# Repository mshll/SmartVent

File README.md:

# LaunchPilot: Smart Vent

Senior Capstone Project (Spring 2024)

Industry Sponsor: Cedrec Sumimoto

Faculty Advisor: Andrew Greenberg

Team members: Meshal Almutairi, Michael Fontaine, Abdulaziz Alateeqi,
Fawzan Alfahad, John Michael Mertz

## Overview

We teamed up with Launch Pilot to make a smart vent system. The main goal was to ensure safe indoor air quality by monitoring CO2 levels. When the CO2 level goes above the safe threshold, the system automatically activates to circulate fresh clean air into the room, thus reducing the CO2 level.

## Approach

We designed the system using sensors to detect CO2 levels, temperature, and
humidity. The design also includes fans that operate at different speeds to help with fresh air circulations, an LCD to display the sensor readings, and a microcontroller as the brain of this project. We also implemented a web-based dashboard that is accessible via a local network for remote monitoring and adjustments such as changing the CO2 level threshold, turning the system entirely on or off, and controlling the fan's speed. Additionally, we integrated buttons on the fans to provide direct control for the different settings.

## Results

Our system successfully reads carbon dioxide levels and activates the fans accordingly. Moreover, the web-based dashboard and the buttons work great when adjusting different settings. The LCD provides real-time readings from the sensors as well as any warnings. Users can control the system directly or remotely, which has been a major plus.

## Completed Build

## Dashboard Preview

## Device OLED Display Preview

## Project Report

For more details on the project, please refer to the [Project Report](Documents/Smart_Vent_Report.pdf)

## User Manual

For instructions on how to use the system, please refer to the [User Manual](Documents/Smart_Vent_User_Manual.pdf)

## License

This project is licensed under the AGPL-3.0 License - see the [LICENSE](LICENSE) file for details.

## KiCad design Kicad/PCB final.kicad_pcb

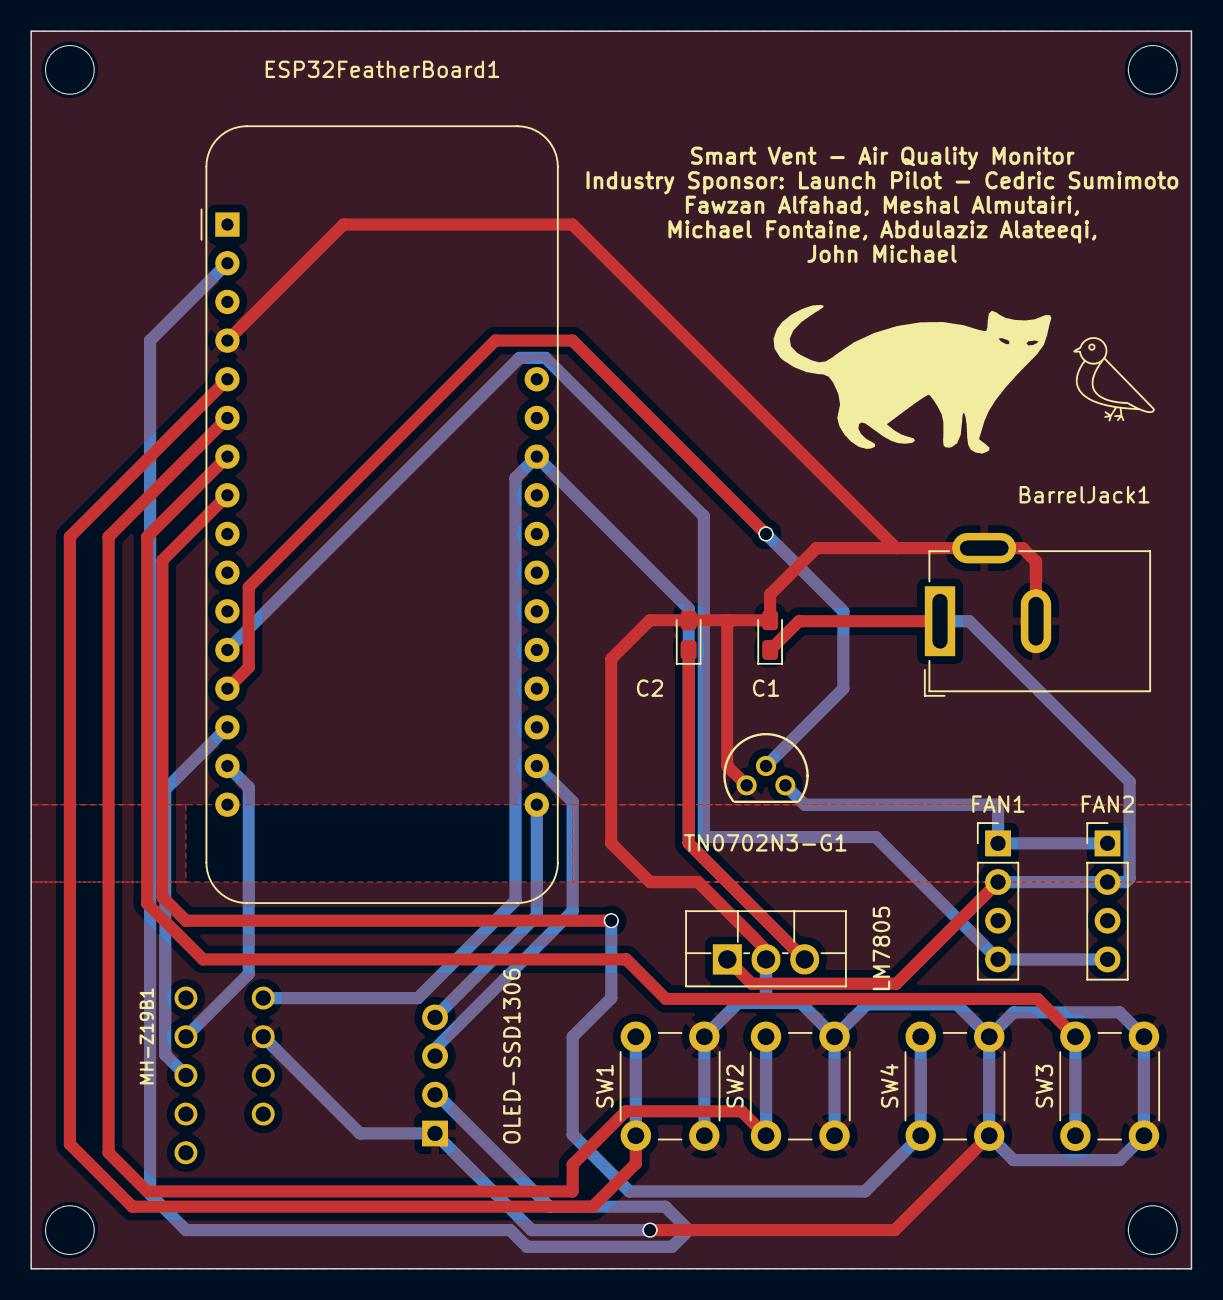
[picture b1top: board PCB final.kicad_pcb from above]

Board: 2 copper layers, 76.2 x 81.3 mm, 14 parts (0 on the bottom side), 15 nets.

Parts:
BarrelJack1: BarrelJack_GCT_DCJ200-10-A_Horizontal
C1: 0.1pF; CP_EIA-2012-12_Kemet-R_Pad1.30x1.05mm_HandSolder
C2: 0.47pF; CP_EIA-2012-12_Kemet-R_Pad1.30x1.05mm_HandSolder
ESP32FeatherBoard1: Adafruit_Feather
FAN1, FAN2: PinHeader_1x04_P2.54mm_Vertical
LM7805: TO-220F-3_Vertical
MH-Z19B1: MH-Z19B-FOOT
OLED-SSD1306: Adafruit_SSD1306
SW1, SW2, SW3, SW4: SW_PUSH_6mm_H4.3mm
TN0702N3-G1: TO-92_MC_MCH

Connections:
FAN1 (GND): FAN1.1, FAN2.1, TN0702N3-G1.3 (DRAIN)
FAN (PWM): ESP32FeatherBoard1.12 (MOSI/IO18), FAN1.4, FAN2.4
GND: BarrelJack1.2, BarrelJack1.3, C1.2, C2.2, ESP32FeatherBoard1.4 (GND), LM7805.2 (GND), MH-Z19B1.GND, OLED-SSD1306.1 (GND), SW1.2, SW2.2, SW3.2, SW4.2, TN0702N3-G1.1 (SOURCE)
unnamed: ESP32FeatherBoard1.2 (3V3), OLED-SSD1306.2 (VCC)
unnamed: ESP32FeatherBoard1.6 (DAC1/A1), SW2.1
unnamed: ESP32FeatherBoard1.5 (DAC2/A0), SW1.1
unnamed: ESP32FeatherBoard1.7 (I34/A2), SW3.1
unnamed: ESP32FeatherBoard1.8 (I39/A3), SW4.1
unnamed: ESP32FeatherBoard1.13 (MISO/IO19), TN0702N3-G1.2 (GATE)
unnamed: ESP32FeatherBoard1.14 (RX/IO16), MH-Z19B1.TX
unnamed: ESP32FeatherBoard1.18 (SCL/IO22), OLED-SSD1306.3 (SCL)
unnamed: ESP32FeatherBoard1.17 (SDA/IO23), OLED-SSD1306.4 (SDA)
unnamed: ESP32FeatherBoard1.15 (TX/IO17), MH-Z19B1.RX
unnamed: BarrelJack1.1, C2.1, FAN1.2, FAN2.2, LM7805.1 (IN)
USB: C1.1, ESP32FeatherBoard1.26 (USB), LM7805.3 (OUT), MH-Z19B1.VIN

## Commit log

2024-01-13 add project doc
2024-01-14 Create LICENSE
2024-01-28 Simple MQ135 test code
2024-01-28 setup platformio
2024-01-28 datasheet added mq135
2024-01-29 esp32 pinouts added
2024-01-31 setup OLED
2024-02-01 fans test code
2024-02-01 add climate module runs a task that measures climate periodically
2024-02-01 add oled module
2024-02-01 add co2 & environment modules
2024-02-05 update MQ135 calibration
2024-02-05 initial dashboard setup
2024-02-25 update ESP-DASH
2024-02-25 update ESPConnect
2024-02-25 modify ESPConnect & update OLED UI
2024-02-25 add air and push button cards to dashboard
2024-02-25 basicFour_Buttons.ino is for the four buttons
    This is a basic test for the four buttons. This requires four pins for reading.
2024-03-01 added relay stuff to completely turn fans off
2024-03-01 initial fan integration, still TODO also add simple oled toggle
2024-03-02 prototype layout
2024-03-02 added Buttons2 library
2024-03-02 made the code use Button2 library
2024-03-17 added menu_nav_test
2024-03-17 added button2 library to it and uncommented delays
2024-03-20 added idle timer interrupt narrowed button press type needs
2024-03-21 initial navigation menu complete
2024-04-24 added TODO's to things that needed to be done for implementations.
2024-04-25 added sleep button
2024-04-26 added display function for CO2 Levels Options
2024-04-26 added Display to Fan Speed
2024-04-26 changed some minor display types
2024-04-27 initial multi-device support implemented udp to broadcast and receieve mac addresses from other devices on the same network and elect host board
2024-04-30 fix multi-device support
2024-05-01 implement webserver class
2024-05-02 update dashboard for multi-device support
2024-05-02 update dashboard hub page frontend
2024-05-02 update webserver to serialize devices for dashboard
2024-05-03 update dashboard frontend design
2024-05-03 update dashboard - add vent info to stats - show device name + active devices count - change fan card - add air quality
2024-05-03 implement automatic time setup, change esp32 partition scheme using ntp server and worldtimeapi.org for time setup
2024-05-03 implement data logging and visualization
2024-05-04 menu_nav stuff
2024-05-04 update pins for 1st iteration build, fix bugs, add fan override option
2024-05-05 use new mh-z19b sensor
2024-05-06 remove old sensors code & dependencies
2024-05-08 fix tickers
2024-05-09 Add Kicad files
2024-05-10 Add Kicad files (Updated)
2024-05-10 move Kicad drill files
2024-05-10 update data logging and chart design
2024-05-18 make fans and oled classes, add common
2024-05-18 make dashboard a class, add option to toggle temp units
2024-05-18 initial version of nav.h file
2024-05-19 bug fix, change co2 thresholds
2024-05-19 implement initial simple menu
2024-05-19 discarded the usage of FirstPage()
2024-05-31 [incomplete] - testing termperature unit
2024-06-01 update UI, fix fans bug
2024-06-03 added menu screen for Temp Units + put oled loop to core + added dashboard.h to dashboard.cpp
2024-06-04 fixed ESPdash includes in both dashboard files
2024-06-07 finished buttons for changing Termperature Unit
2024-06-07 little coding compression
2024-06-07 added Fan Override Control
2024-06-07 added a simple Wifi Reset option
2024-06-07 added simple wifi details ** Needs TODO: Display WIFI Details when connected.
2024-06-09 flipped increment and decrement for Fan Speed Override, added to display IP Address when connected to wifi, failed to add MAC Address
2024-06-14 implement preferences manager to make options persistent, finish wifi info screen, bug fixes
